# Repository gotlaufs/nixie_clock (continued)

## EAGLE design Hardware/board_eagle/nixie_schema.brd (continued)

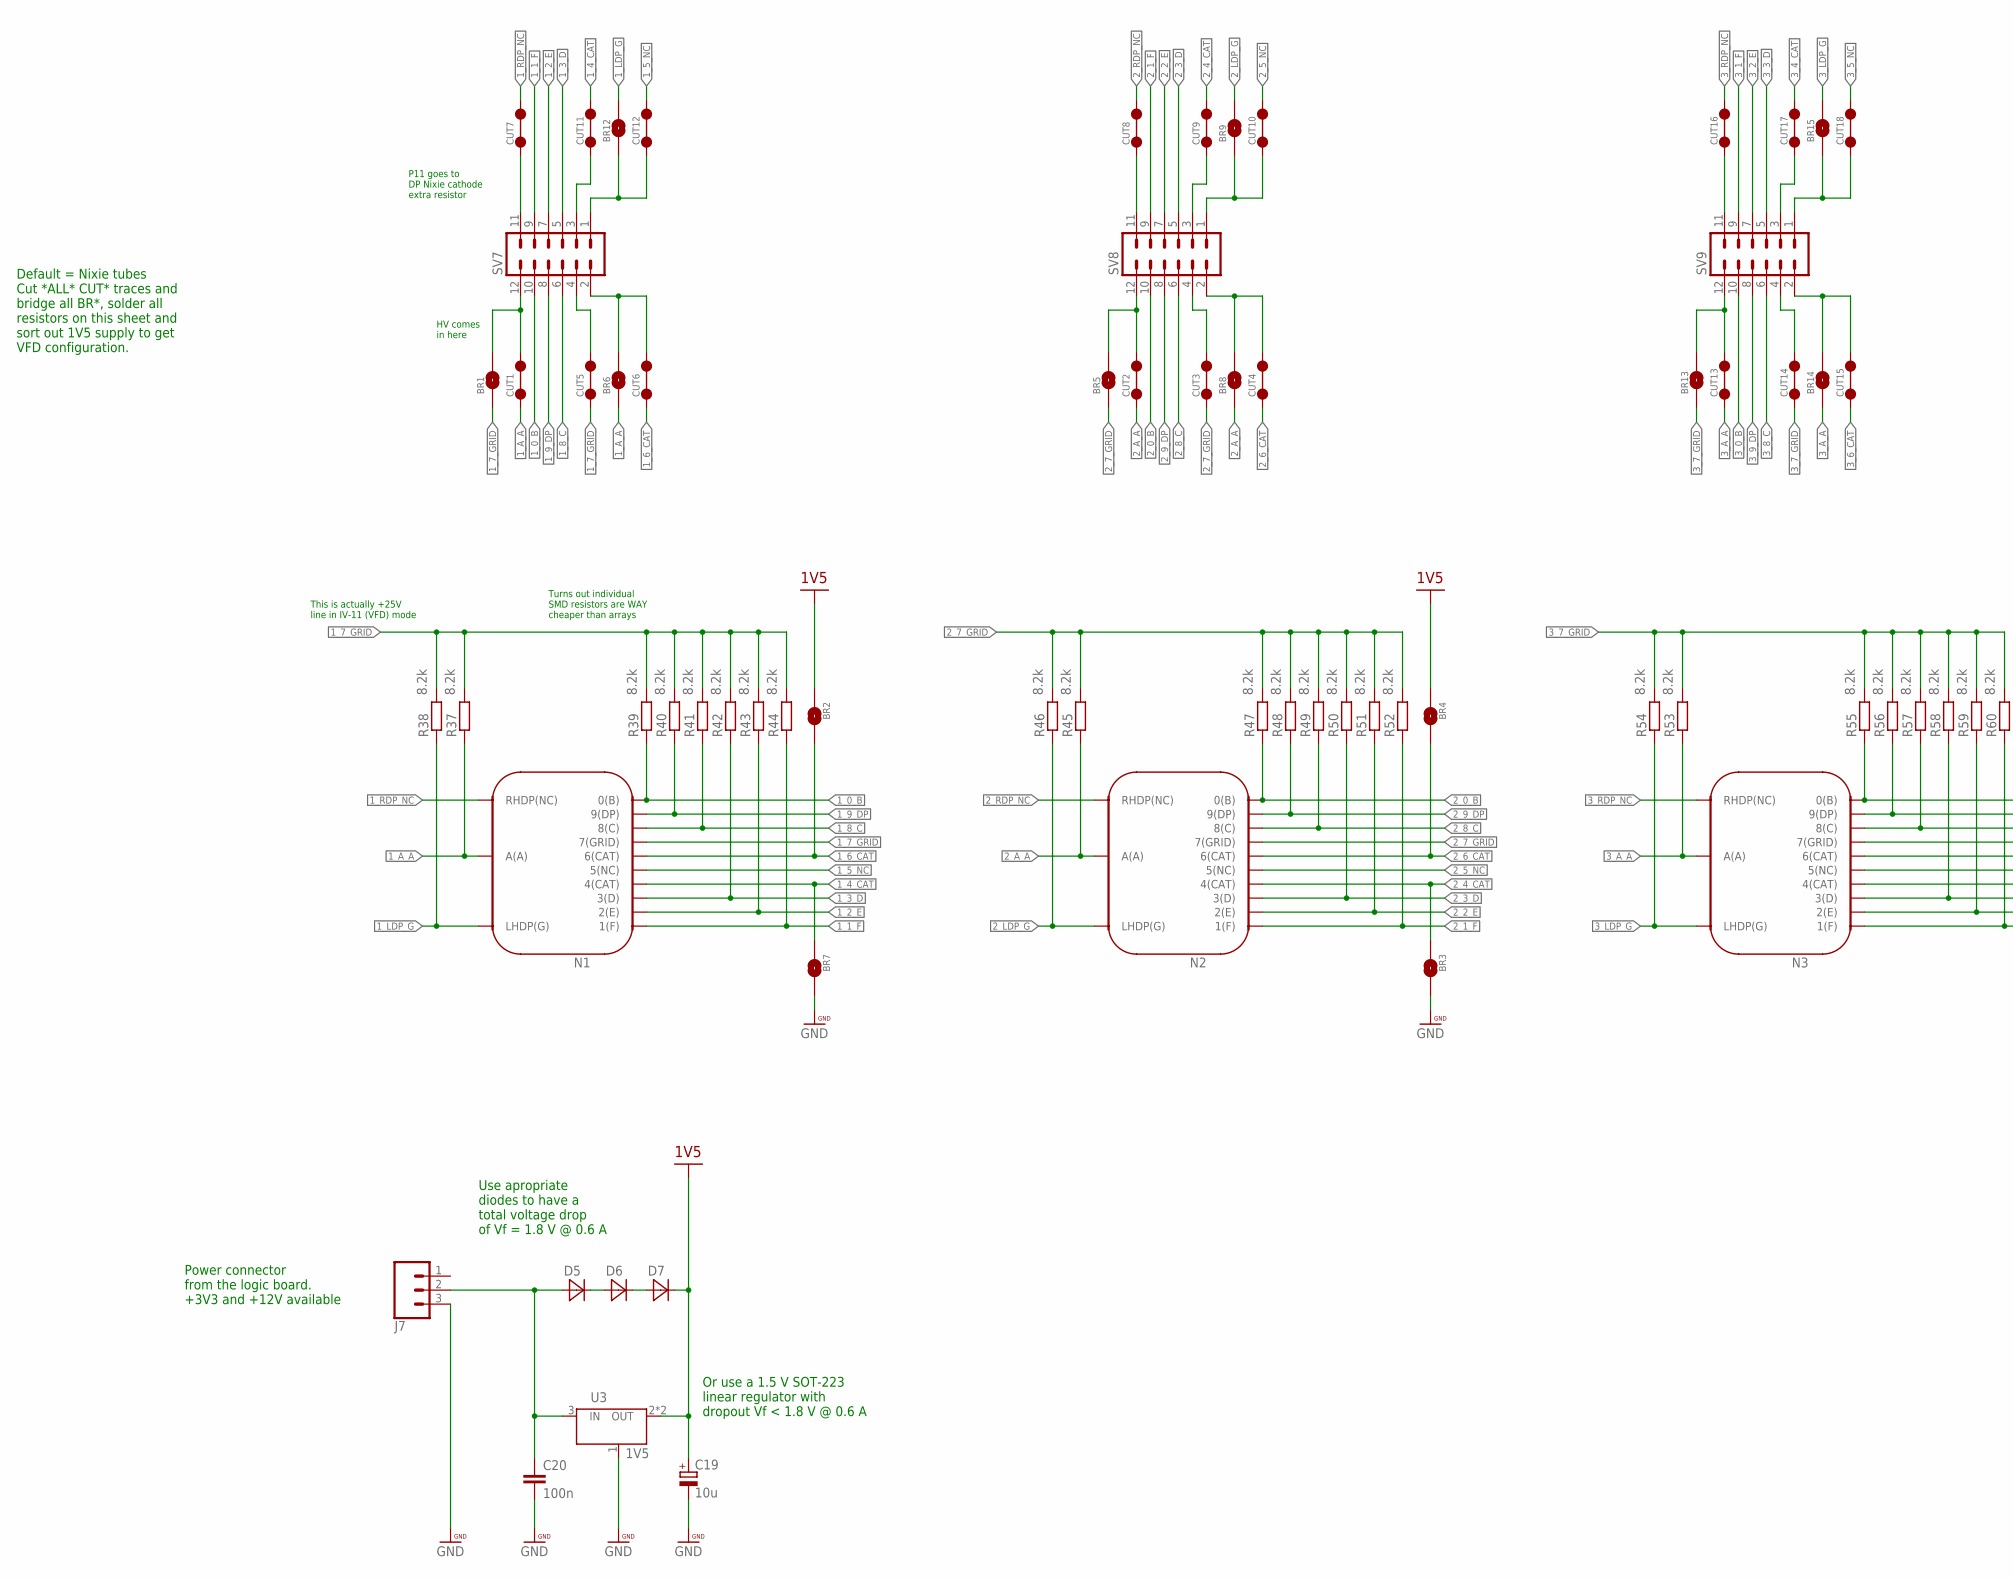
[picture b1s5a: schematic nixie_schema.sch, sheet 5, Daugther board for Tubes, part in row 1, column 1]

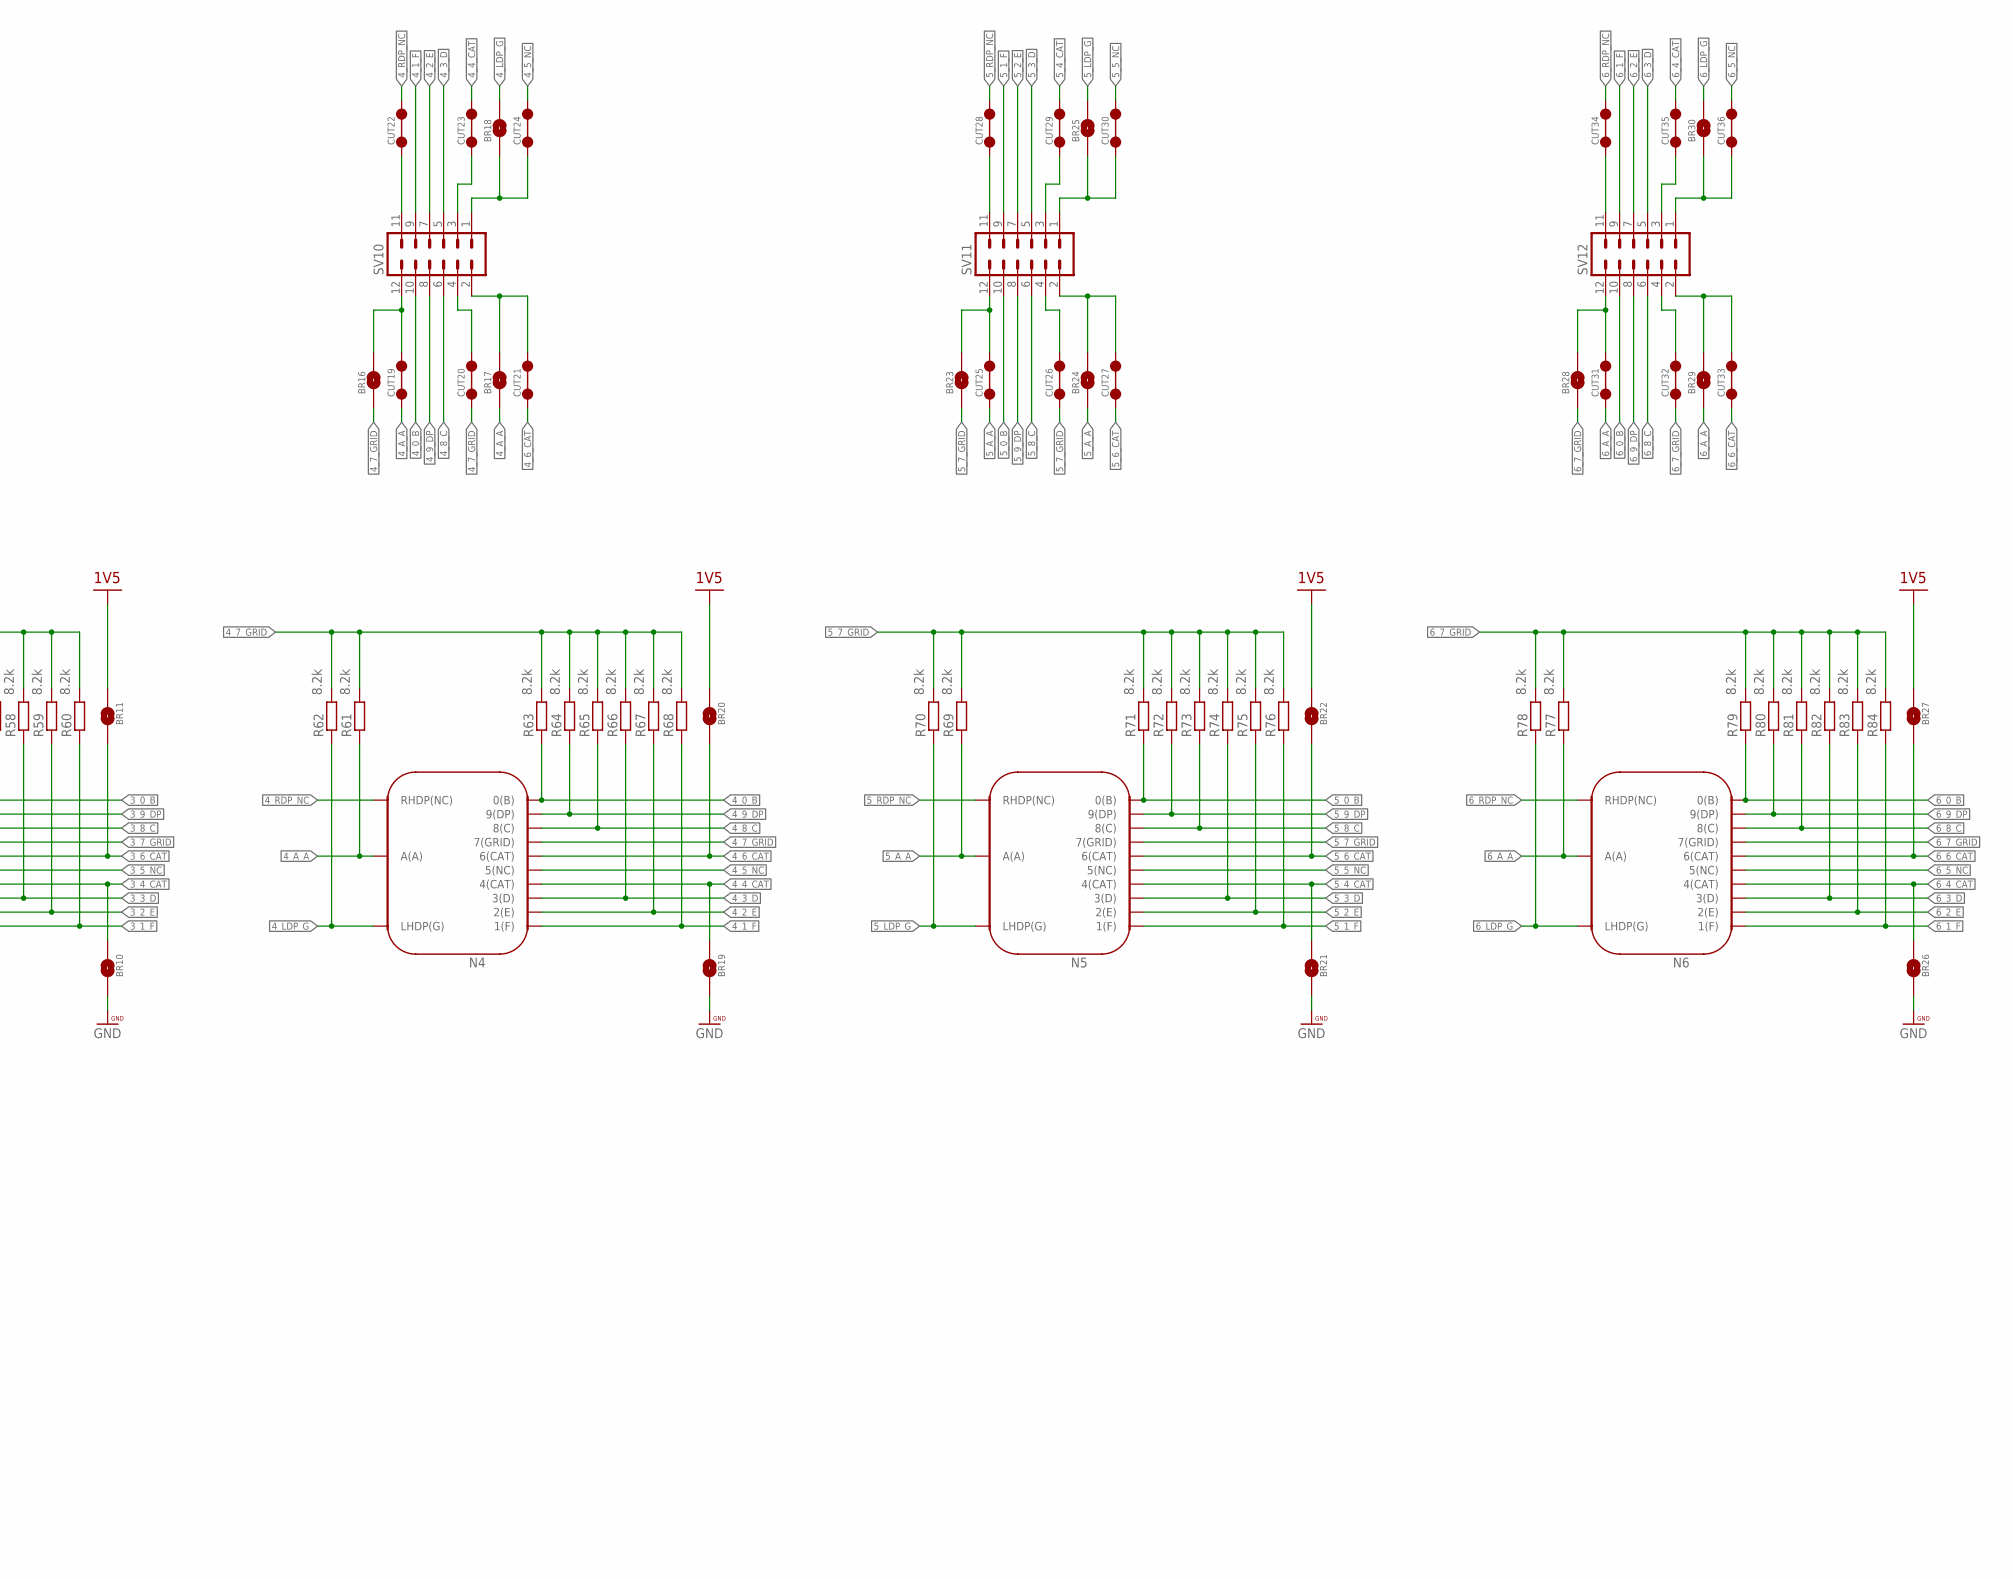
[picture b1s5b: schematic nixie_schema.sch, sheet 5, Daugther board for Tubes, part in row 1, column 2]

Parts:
BR1, BR2, BR3, BR4, BR5, BR6, BR7, BR8, BR9, BR10, BR11, BR12, BR13, BR14, BR15, BR16, BR17, BR18, BR19, BR20, BR21, BR22, BR23, BR24, BR25, BR26, BR27, BR28, BR29, BR30: HV_SOLDER_BRIDGE
C19: 10u; 153CLV-1014
C20: 100n; C0805
CUT1, CUT2, CUT3, CUT4, CUT5, CUT6, CUT7, CUT8, CUT9, CUT10, CUT11, CUT12, CUT13, CUT14, CUT15, CUT16, CUT17, CUT18, CUT19, CUT20, CUT21, CUT22, CUT23, CUT24, CUT25, CUT26, CUT27, CUT28, CUT29, CUT30, CUT31, CUT32, CUT33, CUT34, CUT35, CUT36: CUT_TRACE; CUT_TRACE_2
D5, D6, D7: B230A-13-F; SMA/SMB
J7: CONN_03; 1X03
N1, N2, N3, N4, N5, N6: IN-14_IV-11_COMBI; IN-14_IV-11
R37, R38, R39, R40, R41, R42, R43, R44, R45, R46, R47, R48, R49, R50, R51, R52, R53, R54, R55, R56, R57, R58, R59, R60, R61, R62, R63, R64, R65, R66, R67, R68, R69, R70, R71, R72, R73, R74, R75, R76, R77, R78, R79, R80, R81, R82, R83, R84: 8.2k; R0603
SV7, SV8, SV9, SV10, SV11, SV12: MA06-2
U3: 1V5; SOT223

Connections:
1V5: BR2.P$1 (1), BR4.P$1 (1), BR11.P$1 (1), BR20.P$1 (1), BR22.P$1 (1), BR27.P$1 (1), C19.+, D7.C, U3.2 (OUT), U3.4 (OUT)
1_0_B: N1.0(B), R39.1, SV7.10
1_1_F: N1.1(F), R44.1, SV7.9
1_2_E: N1.2(E), R43.1, SV7.7
1_3_D: N1.3(D), R42.1, SV7.5
1_4_CAT: BR7.P$1 (1), CUT11.P$2 (2), N1.4(CAT)
1_5_NC: CUT12.P$2 (2), N1.5(NC)
1_6_CAT: BR2.P$2 (2), CUT6.P$1 (1), N1.6(CAT)
1_7_GRID: BR1.P$1 (1), CUT5.P$1 (1), N1.7(GRID), R37.2, R38.2, R39.2, R40.2, R41.2, R42.2, R43.2, R44.2
1_8_C: N1.8(C), R41.1, SV7.6
1_9_DP: N1.9(DP), R40.1, SV7.8
1_A_A: BR6.P$1 (1), CUT1.P$1 (1), N1.A(A), R37.1
1_LDP_G: BR12.P$2 (2), N1.LHDP(G), R38.1
1_RDP_NC: CUT7.P$2 (2), N1.RHDP(NC)
2_0_B: N2.0(B), R47.1, SV8.10
2_1_F: N2.1(F), R52.1, SV8.9
2_2_E: N2.2(E), R51.1, SV8.7
2_3_D: N2.3(D), R50.1, SV8.5
2_4_CAT: BR3.P$1 (1), CUT9.P$2 (2), N2.4(CAT)
2_5_NC: CUT10.P$2 (2), N2.5(NC)
2_6_CAT: BR4.P$2 (2), CUT4.P$1 (1), N2.6(CAT)
2_7_GRID: BR5.P$1 (1), CUT3.P$1 (1), N2.7(GRID), R45.2, R46.2, R47.2, R48.2, R49.2, R50.2, R51.2, R52.2
2_8_C: N2.8(C), R49.1, SV8.6
2_9_DP: N2.9(DP), R48.1, SV8.8
2_A_A: BR8.P$1 (1), CUT2.P$1 (1), N2.A(A), R45.1
2_LDP_G: BR9.P$2 (2), N2.LHDP(G), R46.1
2_RDP_NC: CUT8.P$2 (2), N2.RHDP(NC)
3_0_B: N3.0(B), R55.1, SV9.10
3_1_F: N3.1(F), R60.1, SV9.9
3_2_E: N3.2(E), R59.1, SV9.7
3_3_D: N3.3(D), R58.1, SV9.5
3_4_CAT: BR10.P$1 (1), CUT17.P$2 (2), N3.4(CAT)
3_5_NC: CUT18.P$2 (2), N3.5(NC)
3_6_CAT: BR11.P$2 (2), CUT15.P$1 (1), N3.6(CAT)
3_7_GRID: BR13.P$1 (1), CUT14.P$1 (1), N3.7(GRID), R53.2, R54.2, R55.2, R56.2, R57.2, R58.2, R59.2, R60.2
3_8_C: N3.8(C), R57.1, SV9.6
3_9_DP: N3.9(DP), R56.1, SV9.8
3_A_A: BR14.P$1 (1), CUT13.P$1 (1), N3.A(A), R53.1
3_LDP_G: BR15.P$2 (2), N3.LHDP(G), R54.1
3_RDP_NC: CUT16.P$2 (2), N3.RHDP(NC)
4_0_B: N4.0(B), R63.1, SV10.10
4_1_F: N4.1(F), R68.1, SV10.9
4_2_E: N4.2(E), R67.1, SV10.7
4_3_D: N4.3(D), R66.1, SV10.5
4_4_CAT: BR19.P$1 (1), CUT23.P$2 (2), N4.4(CAT)
4_5_NC: CUT24.P$2 (2), N4.5(NC)
4_6_CAT: BR20.P$2 (2), CUT21.P$1 (1), N4.6(CAT)
4_7_GRID: BR16.P$1 (1), CUT20.P$1 (1), N4.7(GRID), R61.2, R62.2, R63.2, R64.2, R65.2, R66.2, R67.2, R68.2
4_8_C: N4.8(C), R65.1, SV10.6
4_9_DP: N4.9(DP), R64.1, SV10.8
4_A_A: BR17.P$1 (1), CUT19.P$1 (1), N4.A(A), R61.1
4_LDP_G: BR18.P$2 (2), N4.LHDP(G), R62.1
4_RDP_NC: CUT22.P$2 (2), N4.RHDP(NC)
5_0_B: N5.0(B), R71.1, SV11.10
5_1_F: N5.1(F), R76.1, SV11.9
5_2_E: N5.2(E), R75.1, SV11.7
5_3_D: N5.3(D), R74.1, SV11.5
5_4_CAT: BR21.P$1 (1), CUT29.P$2 (2), N5.4(CAT)
5_5_NC: CUT30.P$2 (2), N5.5(NC)
5_6_CAT: BR22.P$2 (2), CUT27.P$1 (1), N5.6(CAT)
5_7_GRID: BR23.P$1 (1), CUT26.P$1 (1), N5.7(GRID), R69.2, R70.2, R71.2, R72.2, R73.2, R74.2, R75.2, R76.2
5_8_C: N5.8(C), R73.1, SV11.6
5_9_DP: N5.9(DP), R72.1, SV11.8
5_A_A: BR24.P$1 (1), CUT25.P$1 (1), N5.A(A), R69.1
5_LDP_G: BR25.P$2 (2), N5.LHDP(G), R70.1
5_RDP_NC: CUT28.P$2 (2), N5.RHDP(NC)
6_0_B: N6.0(B), R79.1, SV12.10
6_1_F: N6.1(F), R84.1, SV12.9
6_2_E: N6.2(E), R83.1, SV12.7
6_3_D: N6.3(D), R82.1, SV12.5
6_4_CAT: BR26.P$1 (1), CUT35.P$2 (2), N6.4(CAT)
6_5_NC: CUT36.P$2 (2), N6.5(NC)
6_6_CAT: BR27.P$2 (2), CUT33.P$1 (1), N6.6(CAT)
6_7_GRID: BR28.P$1 (1), CUT32.P$1 (1), N6.7(GRID), R77.2, R78.2, R79.2, R80.2, R81.2, R82.2, R83.2, R84.2
6_8_C: N6.8(C), R81.1, SV12.6
6_9_DP: N6.9(DP), R80.1, SV12.8
6_A_A: BR29.P$1 (1), CUT31.P$1 (1), N6.A(A), R77.1
6_LDP_G: BR30.P$2 (2), N6.LHDP(G), R78.1
6_RDP_NC: CUT34.P$2 (2), N6.RHDP(NC)
GND: BR3.P$2 (2), BR7.P$2 (2), BR10.P$2 (2), BR19.P$2 (2), BR21.P$2 (2), BR26.P$2 (2), C19.-, C20.2, J7.3, U3.1 (GND/ADJ); also elsewhere on the board
unnamed: BR5.P$2 (2), CUT2.P$2 (2), SV8.12
unnamed: BR1.P$2 (2), CUT1.P$2 (2), SV7.12
unnamed: BR8.P$2 (2), CUT4.P$2 (2), SV8.2
unnamed: CUT3.P$2 (2), SV8.4
unnamed: BR6.P$2 (2), CUT6.P$2 (2), SV7.2
unnamed: CUT8.P$1 (1), SV8.11
unnamed: BR13.P$2 (2), CUT13.P$2 (2), SV9.12
unnamed: BR9.P$1 (1), CUT10.P$1 (1), SV8.1
unnamed: CUT5.P$2 (2), SV7.4
unnamed: CUT9.P$1 (1), SV8.3
unnamed: CUT7.P$1 (1), SV7.11
unnamed: BR14.P$2 (2), CUT15.P$2 (2), SV9.2
unnamed: CUT14.P$2 (2), SV9.4
unnamed: BR12.P$1 (1), CUT12.P$1 (1), SV7.1
unnamed: CUT11.P$1 (1), SV7.3
unnamed: CUT16.P$1 (1), SV9.11
unnamed: BR15.P$1 (1), CUT18.P$1 (1), SV9.1
unnamed: CUT17.P$1 (1), SV9.3
unnamed: BR16.P$2 (2), CUT19.P$2 (2), SV10.12
unnamed: BR17.P$2 (2), CUT21.P$2 (2), SV10.2
unnamed: CUT20.P$2 (2), SV10.4
unnamed: CUT22.P$1 (1), SV10.11
unnamed: BR18.P$1 (1), CUT24.P$1 (1), SV10.1
unnamed: CUT23.P$1 (1), SV10.3
unnamed: BR23.P$2 (2), CUT25.P$2 (2), SV11.12
unnamed: BR24.P$2 (2), CUT27.P$2 (2), SV11.2
unnamed: CUT26.P$2 (2), SV11.4
unnamed: CUT28.P$1 (1), SV11.11
unnamed: BR25.P$1 (1), CUT30.P$1 (1), SV11.1
unnamed: BR28.P$2 (2), CUT31.P$2 (2), SV12.12
unnamed: CUT29.P$1 (1), SV11.3
unnamed: BR29.P$2 (2), CUT33.P$2 (2), SV12.2
unnamed: CUT32.P$2 (2), SV12.4
unnamed: CUT34.P$1 (1), SV12.11
unnamed: BR30.P$1 (1), CUT36.P$1 (1), SV12.1
unnamed: CUT35.P$1 (1), SV12.3
unnamed: C20.1, D5.A, J7.2, U3.3 (IN)
unnamed: D5.C, D6.A
unnamed: D6.C, D7.A

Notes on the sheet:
Power connector from the logic board. +3V3 and +12V available
Use apropriate diodes to have a total voltage drop of Vf = 1.8 V @ 0.6 A
Or use a 1.5 V SOT-223 linear regulator with dropout Vf < 1.8 V @ 0.6 A
Default = Nixie tubes Cut *ALL* CUT* traces and bridge all BR*, solder all resistors on this sheet and sort out 1V5 supply to get VFD configuration.
HV comes in here
P11 goes to DP Nixie cathode extra resistor
Turns out individual SMD resistors are WAY cheaper than arrays
This is actually +25V line in IV-11 (VFD) mode

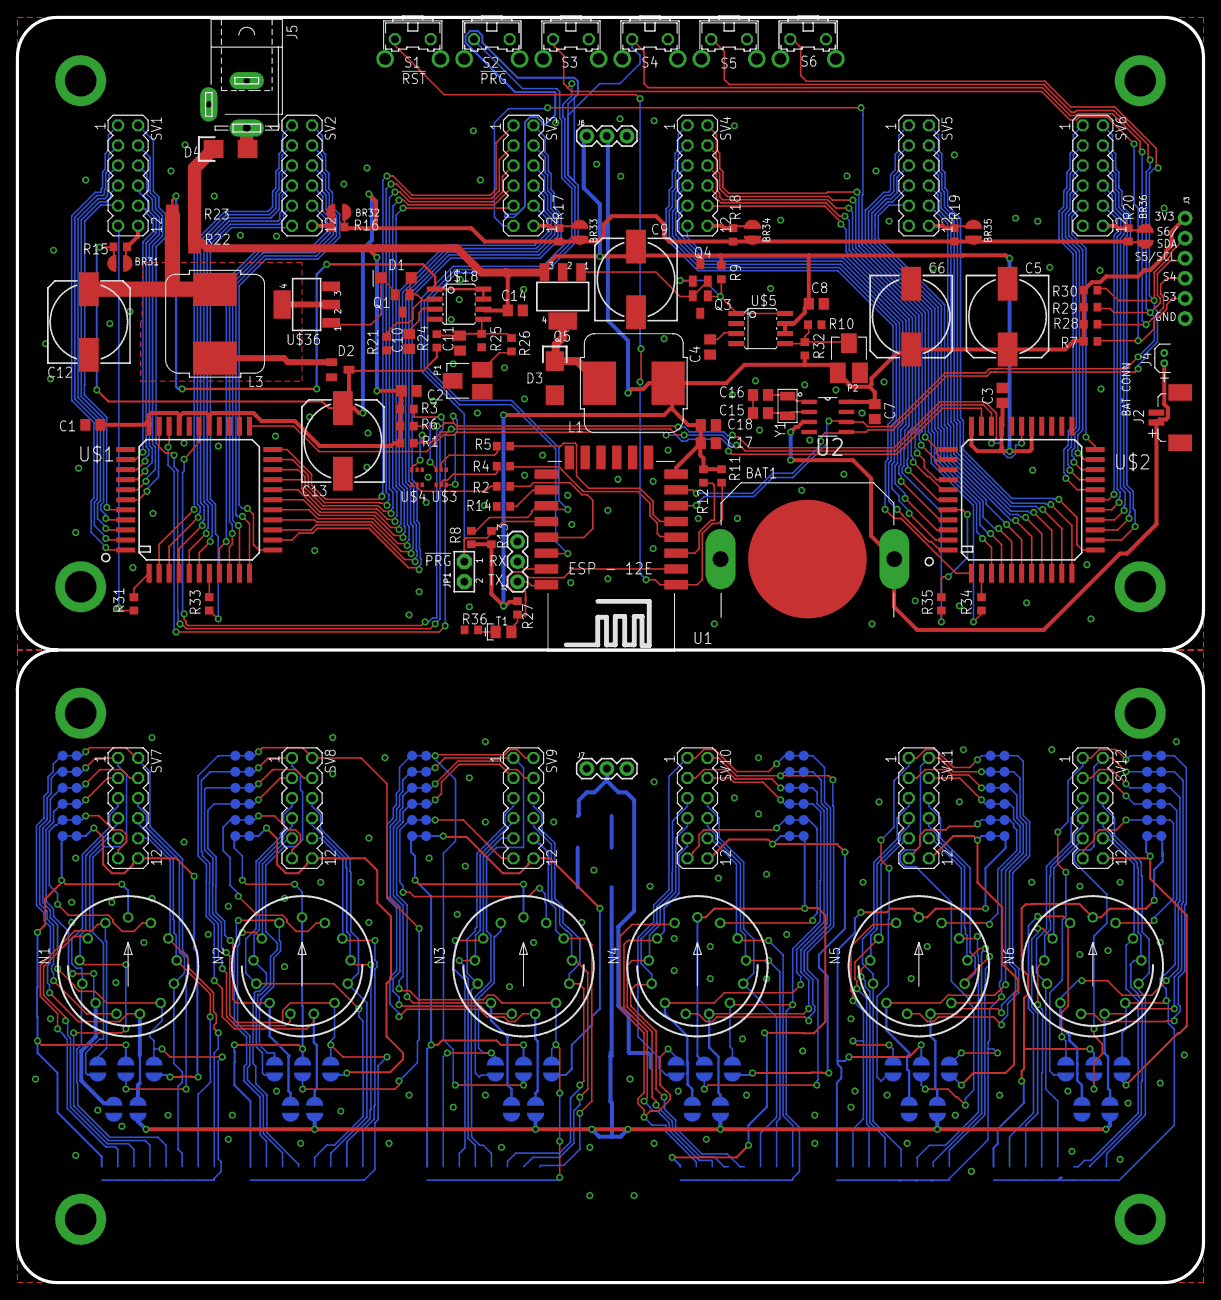
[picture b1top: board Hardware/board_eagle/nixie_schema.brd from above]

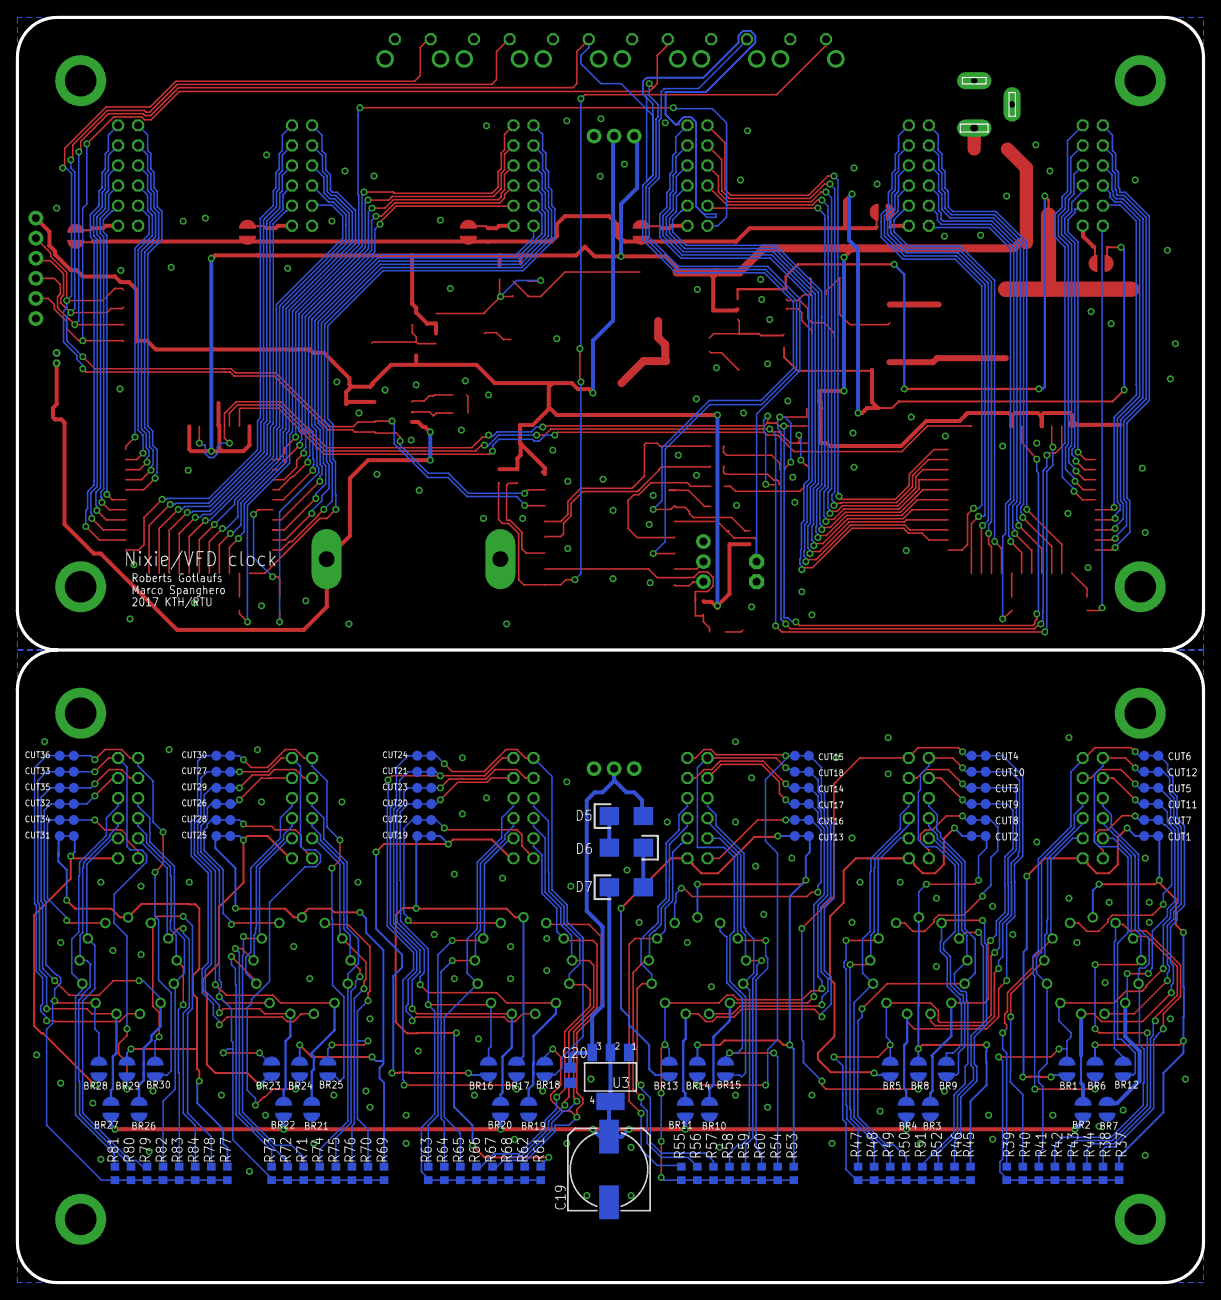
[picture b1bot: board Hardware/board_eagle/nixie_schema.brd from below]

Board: 2 copper layers, 150.0 x 160.0 mm, 236 parts (120 on the bottom side), 234 nets.

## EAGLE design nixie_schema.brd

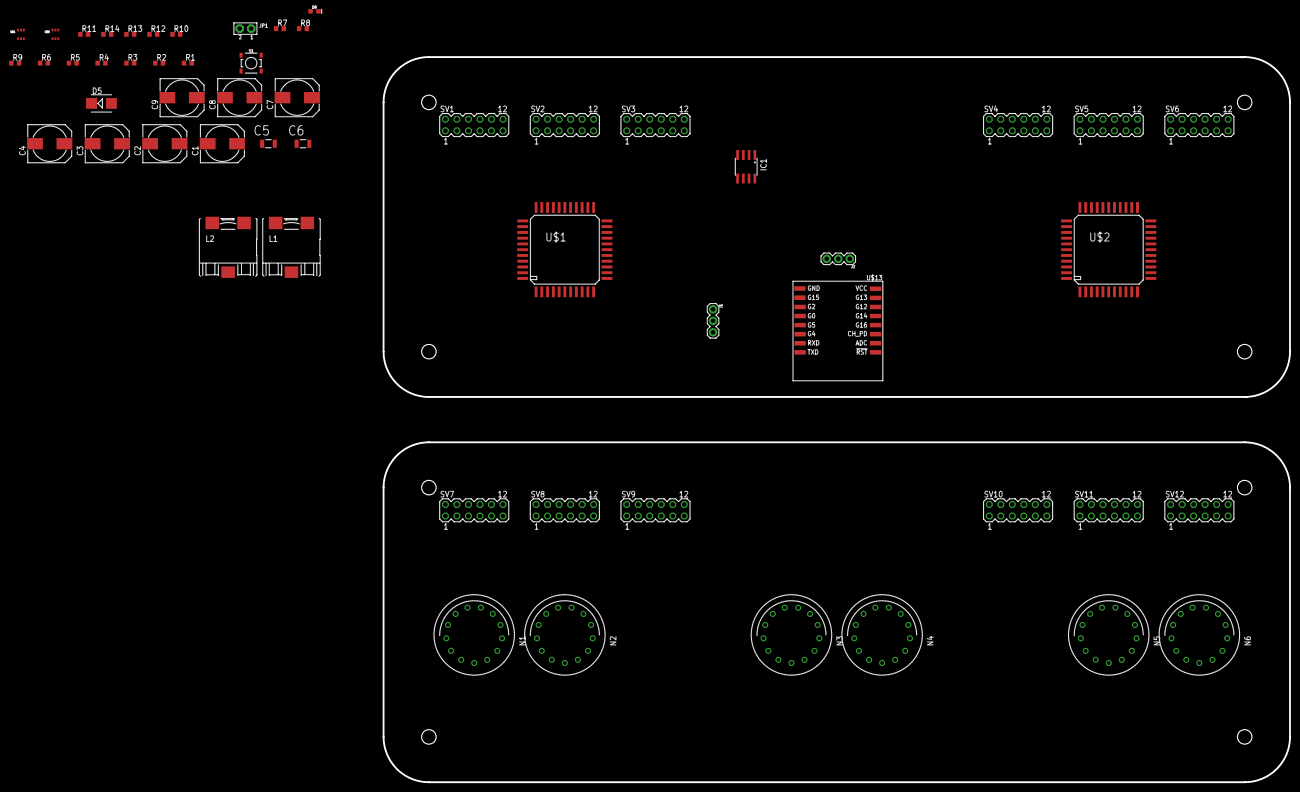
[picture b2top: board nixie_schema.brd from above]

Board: 2 copper layers, 200.0 x 160.0 mm, 55 parts (0 on the bottom side), 148 nets, no tracks yet.

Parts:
C1, C2, C3: 100n; 140CLH-0810
C4, C7, C8: 100u; 140CLH-0810
C5: 0.01; CAPC3216X180N
C6: 0.022; CAPC3216X180N
C9: 140CLH-0810
D5: MBRS130LT3; SMB
D6: LED-0603
IC1: LM2672M; SO08
J1, J2: 1X03
JP1: JUMPER2
L1: 100u; CEP125
L2: 4.7u; CEP125
N1, N2, N3, N4, N5, N6: IN-14
R1, R2, R3, R4, R5, R6: 2.21K; R0603
R7: 150; R0603
R8: 1.33k; R0603
R9: 2,37K; R0603
R10, R11, R12, R13, R14: R0603
S1: MOMENTARY-SWITCH-SPST-SMD-4.5MM; TACTILE_SWITCH_SMD_4.5MM
SV1, SV2, SV3, SV4, SV5, SV6, SV7, SV8, SV9, SV10, SV11, SV12: MA06-2
U$1, U$2: HV5522; CQFP-44
U$3, U$4: BSS138DW; SOT-363
U$13: ESP8266-07-12; ESP8266-07W

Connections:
+3V3: C8.+, C9.+, J2.1, L2.2, R10.1, R11.2, R12.2, R13.1, U$13.VCC
DATA_CLK: R5.1, U$13.G14
DATA_IN: R4.1, U$13.G16
DOT_LED: R7.1, U$13.G4
GND: C1.-, C2.-, C3.-, C4.-, C5.1, C7.-, C8.-, C9.-, D5.A, D6.C, IC1.6, J1.3, J2.3, JP1.2, R8.2, R14.1, S1.2, S1.3, U$1.24, U$1.25, U$1.26, U$1.29, U$1.34, U$2.24, U$2.25, U$2.26, U$2.29, U$2.34, U$3.1, U$3.4, U$4.1, U$4.3, U$4.4, U$4.5, U$13.GND
HV_HA_0: SV1.10, U$1.35
HV_HA_1: SV1.8, U$1.36
HV_HA_2: SV1.6, U$1.37
HV_HA_3: SV1.4, U$1.38
HV_HA_4: SV1.2, U$1.39
HV_HA_5: SV1.9, U$1.40
HV_HA_6: SV1.7, U$1.41
HV_HA_7: SV1.5, U$1.42
HV_HA_8: SV1.3, U$1.43
HV_HA_9: SV1.1, U$1.44
HV_HB_0: SV2.10, U$1.1
HV_HB_1: SV2.8, U$1.2
HV_HB_2: SV2.6, U$1.3
HV_HB_3: SV2.4, U$1.5
HV_HB_4: SV2.2, U$1.4
HV_HB_5: SV2.9, U$1.6
HV_HB_6: SV2.7, U$1.7
HV_HB_7: SV2.5, U$1.8
HV_HB_8: SV2.3, U$1.9
HV_HB_9: SV2.1, U$1.10
HV_IN+: SV1.11, SV1.12, SV2.11, SV2.12, SV3.11, SV3.12, SV4.11, SV4.12, SV5.11, SV5.12, SV6.11, SV6.12
HV_MA_0: SV3.10, U$1.11
HV_MA_1: SV3.8, U$1.12
HV_MA_2: SV3.6, U$1.13
HV_MA_3: SV3.4, U$1.14
HV_MA_4: SV3.2, U$1.15
HV_MA_5: SV3.9, U$1.16
HV_MA_6: SV3.7, U$1.17
HV_MA_7: SV3.5, U$1.18
HV_MA_9: SV3.1, U$1.19
HV_MB_0: SV4.10, U$2.35
HV_MB_1: SV4.8, U$2.36
HV_MB_2: SV4.6, U$2.37
HV_MB_3: SV4.4, U$2.38
HV_MB_4: SV4.2, U$2.39
HV_MB_5: SV4.9, U$2.40
HV_MB_6: SV4.7, U$2.41
HV_MB_7: SV4.5, U$2.42
HV_MB_8: SV4.3, U$2.43
HV_MB_9: SV4.1, U$2.44
HV_SA_0: SV5.10, U$2.1
HV_SA_1: SV5.8, U$2.2
HV_SA_2: SV5.6, U$2.3
HV_SA_3: SV5.4, U$2.5
HV_SA_4: SV5.2, U$2.4
HV_SA_5: SV5.9, U$2.6
HV_SA_6: SV5.7, U$2.7
HV_SA_7: SV5.5, U$2.8
HV_SA_8: SV5.3, U$2.9
HV_SA_9: SV5.1, U$2.10
HV_SB_0: SV6.10, U$2.11
HV_SB_1: SV6.8, U$2.12
HV_SB_2: SV6.6, U$2.13
HV_SB_3: SV6.4, U$2.14
HV_SB_4: SV6.2, U$2.15
HV_SB_5: SV6.9, U$2.16
HV_SB_6: SV6.7, U$2.17
HV_SB_7: SV6.5, U$2.18
HV_SB_8: SV6.3, U$2.19
HV_SB_9: SV6.1, U$2.20
LE: R2.1, U$13.G5
unnamed: R3.2, U$1.32, U$3.6
unnamed: R1.2, U$1.31, U$2.31, U$4.6
unnamed: R2.2, U$4.2
unnamed: R4.2, U$3.2
unnamed: C5.2, IC1.2
unnamed: R6.2, U$1.28, U$2.28, U$3.3
unnamed: U$1.23, U$2.32
unnamed: IC1.4, R8.1, R9.2
unnamed: R5.2, U$3.5
unnamed: J2.2, R7.2
unnamed: C6.1, IC1.1
unnamed: C6.2, D5.C, IC1.8, L1.1, R9.1
unnamed: C7.+, L1.2, L2.1
unnamed: R11.1, S1.1, S1.4, U$13.!RST
unnamed: D6.A, R10.2
unnamed: R12.1, U$13.CH_PD
unnamed: J1.1, U$13.TXD
unnamed: J1.2, U$13.RXD
unnamed: R14.2, U$13.G15
unnamed: JP1.1, R13.2, U$13.G0
unnamed: N4.0, SV10.10
unnamed: N1.0, SV7.10
unnamed: N1.1, SV7.8
unnamed: N1.2, SV7.6
unnamed: N1.3, SV7.4
unnamed: N1.4, SV7.2
unnamed: N1.5, SV7.9
unnamed: N1.6, SV7.7
unnamed: N1.7, SV7.5
unnamed: N1.8, SV7.3
unnamed: N1.9, SV7.1
unnamed: N2.9, SV8.1
unnamed: N2.0, SV8.10
unnamed: N2.1, SV8.8
unnamed: N2.2, SV8.6
unnamed: N2.3, SV8.4
unnamed: N2.4, SV8.2
unnamed: N2.5, SV8.9
unnamed: N2.8, SV8.3
unnamed: N2.7, SV8.5
unnamed: N2.6, SV8.7
unnamed: N4.1, SV10.8
unnamed: N3.5, SV9.9
unnamed: N3.6, SV9.7
unnamed: N3.7, SV9.5
unnamed: N3.8, SV9.3
unnamed: N3.9, SV9.1
unnamed: N3.0, SV9.10
unnamed: N3.4, SV9.8
unnamed: N3.3, SV9.6
unnamed: N3.2, SV9.4
unnamed: N3.1, SV9.2
unnamed: N4.2, SV10.6
unnamed: N4.3, SV10.4
unnamed: N4.4, SV10.2
unnamed: N4.5, SV10.9
unnamed: N4.6, SV10.7
unnamed: N4.7, SV10.5
unnamed: N4.8, SV10.3
unnamed: N4.9, SV10.1
unnamed: N5.0, SV11.10
unnamed: N5.1, SV11.8
unnamed: N5.2, SV11.6
unnamed: N5.3, SV11.4
unnamed: N5.4, SV11.2
unnamed: N5.5, SV11.9
unnamed: N5.9, SV11.1
unnamed: N5.8, SV11.3
unnamed: N5.7, SV11.5
unnamed: N5.6, SV11.7
unnamed: N1.A, N2.A, N3.A, N4.A, N5.A, N6.A, SV7.11, SV7.12, SV8.11, SV8.12, SV9.11, SV9.12, SV10.11, SV10.12, SV11.11, SV11.12, SV12.11, SV12.12
unnamed: N6.5, SV12.9
unnamed: N6.6, SV12.7
unnamed: N6.7, SV12.5
unnamed: N6.8, SV12.3
unnamed: N6.9, SV12.1
unnamed: N6.0, SV12.10
unnamed: N6.4, SV12.8
unnamed: N6.3, SV12.6
unnamed: N6.2, SV12.4
unnamed: N6.1, SV12.2
VCC: C1.+, C2.+, C3.+, C4.+, IC1.7, R1.1, R3.1, R6.1, U$1.27, U$1.30, U$1.33, U$2.27, U$2.30, U$2.33

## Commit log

2017-02-08 HV power supply prototype PCB
2017-02-12 Small additions to HV PSU schematic
2017-02-13 Some little additions to footprints
2017-02-15 PCB layout for the HV PSU prototype
2017-02-16 Microscopic trace delete
2017-02-16 Some tweaks to schematic and PCB based on laser etching prototyping
2017-02-17 Edits to some component footprints due to component availability
2017-02-25 Made J1 pads bigger for easier drilling
2017-02-25 BoM for HV PSU prototype
2017-03-01 LTSpice simulation files
2017-03-01 App note for MC34063 regulator
2017-03-01 Newer KiCad format and gitignore for LTSpice
2017-03-10 Make space for the next prototype
2017-03-10 Some reflections on the first HV PSU prototype
2017-03-10 Todo update
2017-03-10 Initial files for HV PSU v2 prototype
2017-03-19 Corrected MOSFET footprint, added test points, made resistor values sane. Also some comments on over-current protection
2017-03-20 PCB for HV PSU v2 prototype
2017-03-28 Added exports for the v2 of HV PCB
2017-03-28 Simulation files for over-current protection
2017-04-02 Initial KiCad schematic for Current Limiter prototype
2017-04-05 Footprints for transistors added
2017-04-05 Datasheets for transistors added
2017-04-05 Added header connectors for OpAmp modules
2017-04-05 Initial over-current PCB layout file
2017-04-06 Overcurrent protection proto PCB mostly done
2017-04-09 Some minor cleanups for OC proto PCB. Added OPAmp daughter board PCB
2017-04-29 Eagle files
    Eagle project files
2017-04-29 Moved Eagle files into appropriate dir
2017-04-29 Fixing minor schematic issues (anode resistors and cap values in 3v3 PSU). Updated gitignore with EAGLE temp files
2017-04-29 Most of HV supply schematic done. Need to pick transistors, caps and diode
2017-05-01 HV PSU schematic captured. Still need to pick correct pot
2017-05-02 Added Buttons
    Added 4 buttons and two strip for connectors. buttons are on the last
    alb gpios. removed connections for DOT_LED
2017-05-03 Changed ESP8266
    changed esp8266 footprint
2017-05-07 Brought Anode resistors to the lower PCB
2017-05-07 Added cheaper 3V3 PSU
2017-05-07 Added optional RTC module and cleaned up the schematic
2017-05-09 Added some footprints
2017-05-09 Rebuilt boards
    Boards are in the correct 150*80 format. repositioned b2b connectors
2017-05-09 Added some more component footprints
2017-05-10 Starting to do layout
2017-05-10 Some more routing
2017-05-10 Routing the PCB
2017-05-11 Top board first route
2017-05-11 Gottom board routing mostly done
2017-05-11 Some more tob board routing
2017-05-11 Mechanical drawing for top and bottom
2017-05-12 Proto for Hinge and first test for enclosure
    Top and bottom SBOK while lateral side needs testing, should fit tough
2017-05-12 Enclosure rev1 finished
2017-05-12 Started fixing nixie tube footprint
2017-05-12 Board 3d and mechanics done
2017-05-13 small fixes
2017-05-13 Top board touting complete
2017-05-13 Added some values to components in schematic
2017-05-15 update on 3d pcb
2017-05-15 hinge rev2.0
2017-05-15 old auto cad version
2017-05-15 fixed hinge
2017-05-15 fixed hinge and saved correctly
2017-05-15 Move mechanical stuff around
2017-05-15 Rename PCB dir appropriately
2017-05-15 Some simulations on beefier 3V3 PSU
2017-05-16 new hinge test
2017-05-16 changed original hinge to 9 taps
2017-05-16 changes to mechanical
    new hinge design for testing. Still breaks
2017-05-16 changed auto cad sw version
2017-05-16 modified wave pattern
2017-05-16 Wave pattern update
2017-05-16 Updated file type
2017-05-16 new test wave
2017-05-18 Modified both switching PSUs for the new VFD requirements
2017-05-18 Modified IN-14 device to accomodate IV-11 VFD
2017-05-18 Added Eagle libraries for components. New symbols for Solder bridge and cut trace comps
2017-05-18 Hopefully fixed compined tube footprint for good
2017-05-18 Added stuff for 1V5 rail for VFD cathodes
2017-05-18 Figured out how to wire up tubes to support both IN-14 and IV-11
2017-05-19 Finished tube schematic layout
2017-05-19 Some initial experimental routing for the top board
2017-05-20 Some more routing of the top board
2017-06-04 Top board routing
2017-06-06 More Tob Board Routing
2017-06-06 Bottom board routing. Some DRC errors remain.
2017-06-13 Most of the board done
2017-06-13 Silk screen touch ups
2017-06-13 More tweaks to silk screen
2017-06-13 CAM job file and first version of Gerbers
